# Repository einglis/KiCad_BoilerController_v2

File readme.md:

# Boiler Controller mk2

A whole new controller retaining the original features:

* Delayed closing valves
* Support for 24vac Nest thermostat (early US model)

And several new features:

* Multiple heating channels (zoned heating)
* ESP8266 for control and scheduling
* Greater flexibility in stat to valve mappings

The main MCU is an ESP8266 running https://github.com/einglis/SimpleNode/tree/main/examples/heating (still a WIP at the time of writing)

The valve controller is an Arduino Nano running https://github.com/einglis/boiler_valves

## HW versions

The first main board (control) had lots of drill holes that were too small; its replacement addesssed this and tidied up a few little details.

The first MCU board had pads that were too tiny to practically solder the transistors; its replacement added bigger pads, deleted the on-board status LEDs (since the MCUs have thier own), and simplified the ctrl+stat selector for the Hot Water valve.

Both replacements fixed an embarassing error where I hadn't read the ordering instructions, leaving a "Order Number Here" label present on both boards  ...along with the actual order numbers.

## v2.1 Pictures

## v2.0 Pictures

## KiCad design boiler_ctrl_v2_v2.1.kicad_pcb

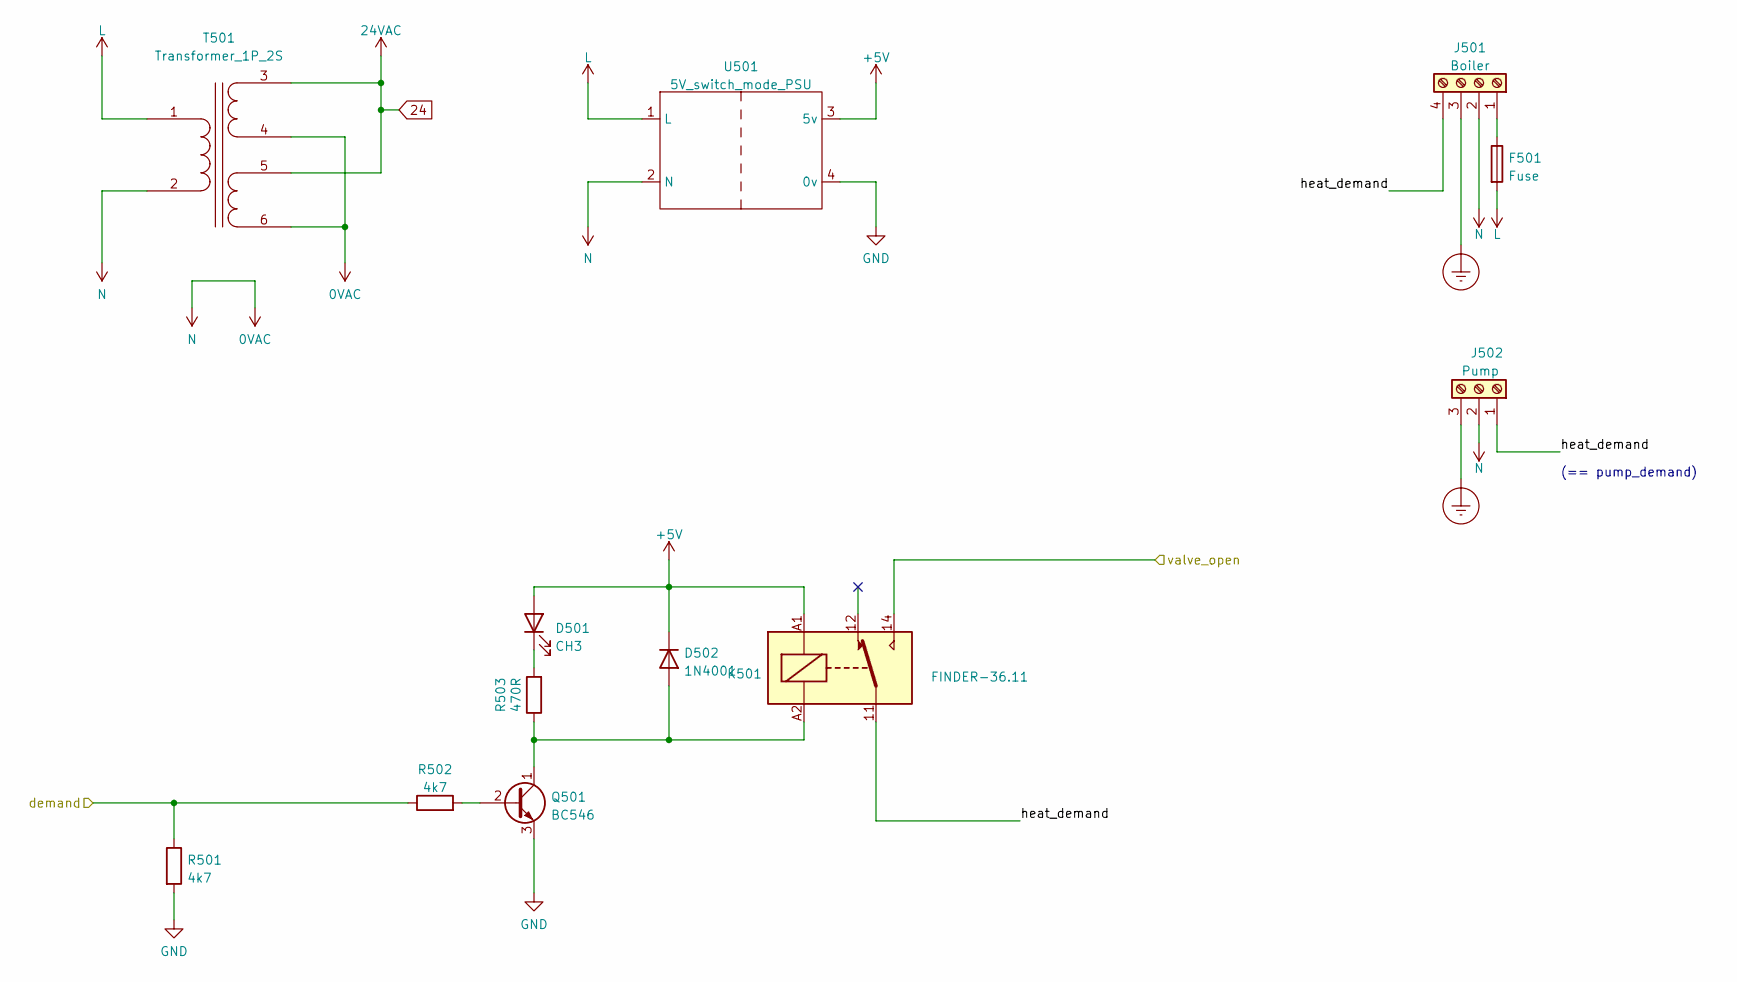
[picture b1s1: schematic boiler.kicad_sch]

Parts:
D501: CH3; LED_1206_3216Metric_Pad1.42x1.75mm_HandSolder
D502: 1N4001; D_DO-41_SOD81_P12mm_Horizontal
F501: Fuse; MULTICORP MC000827
J501: Boiler; CAMDENBOSS CTB0700_4
J502: Pump; CAMDENBOSS CTB0700_3
K501: FINDER-36.11; Relay_SPDT_Finder_36.11
Q501: BC546; TO-92_Inline
R501, R502: 4k7; R_0805_2012Metric_Pad1.20x1.40mm_HandSolder
R503: 470R; R_0805_2012Metric_Pad1.20x1.40mm_HandSolder
T501: Transformer_1P_2S; BLOCK VB_2.8_2_15
U501: 5V_switch_mode_PSU; MYRRA 47122

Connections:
0VAC: J501.2, J502.2, T501.2 (AB), T501.4 (SB), T501.6 (SD), U501.2 (N); also elsewhere on the board
24: T501.3 (SA), T501.5 (SC); also elsewhere on the board
/Boiler etc/heat_demand: J501.4, J502.1, K501.11
/Boiler etc/valve_open: K501.14; also elsewhere on the board
/boiler_demand: R501.1, R502.1; also elsewhere on the board
Earth_Protective: J501.3, J502.3; also elsewhere on the board
GND: Q501.3 (E), R501.2, U501.4 (0v); also elsewhere on the board
LINE: F501.2, T501.1 (AA), U501.1 (L); also elsewhere on the board
unnamed: D501.1 (K), R503.2
unnamed: D502.2 (A), K501.A2, Q501.1 (C), R503.1
unnamed: F501.1, J501.1
unnamed: Q501.2 (B), R502.2

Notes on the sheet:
(== pump_demand)

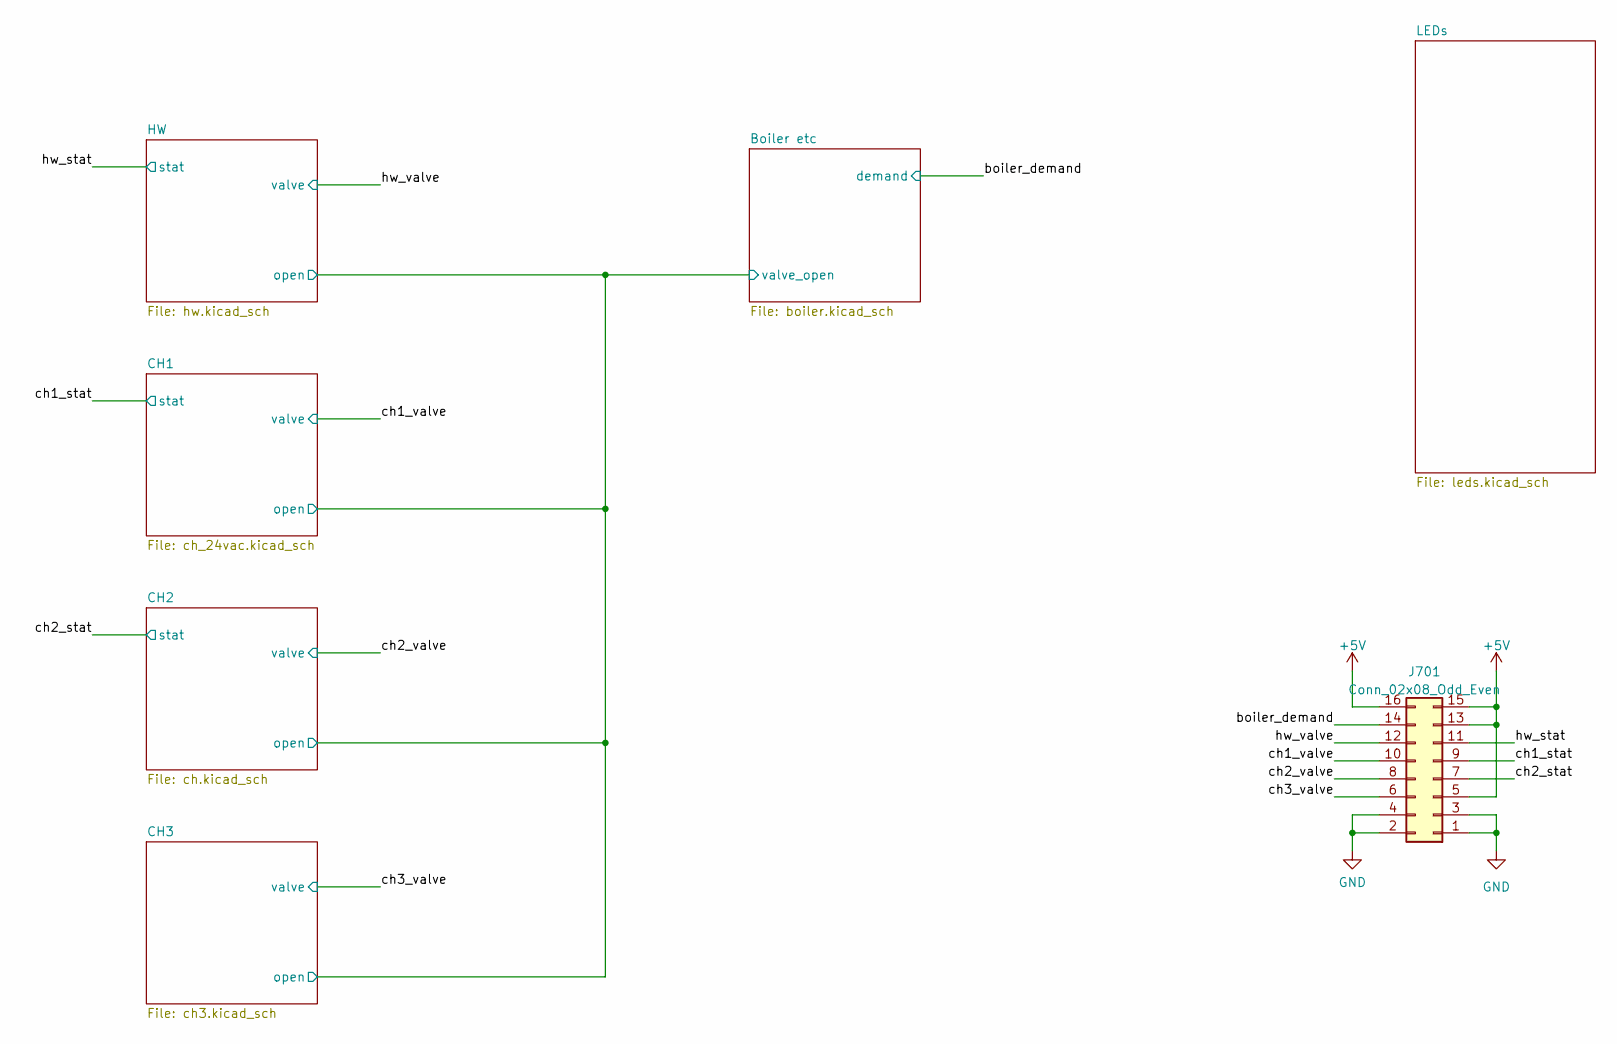
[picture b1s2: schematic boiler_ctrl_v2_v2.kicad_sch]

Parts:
J701: Conn_02x08_Odd_Even; PinHeader_2x08_P2.54mm_Vertical

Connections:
/boiler_demand: J701.14; also elsewhere on the board
/ch1_stat: J701.9; also elsewhere on the board
/ch1_valve: J701.10; also elsewhere on the board
/ch2_stat: J701.7; also elsewhere on the board
/ch2_valve: J701.8; also elsewhere on the board
/ch3_valve: J701.6; also elsewhere on the board
/hw_stat: J701.11; also elsewhere on the board
/hw_valve: J701.12; also elsewhere on the board
GND: J701.1, J701.2, J701.3, J701.4; also elsewhere on the board

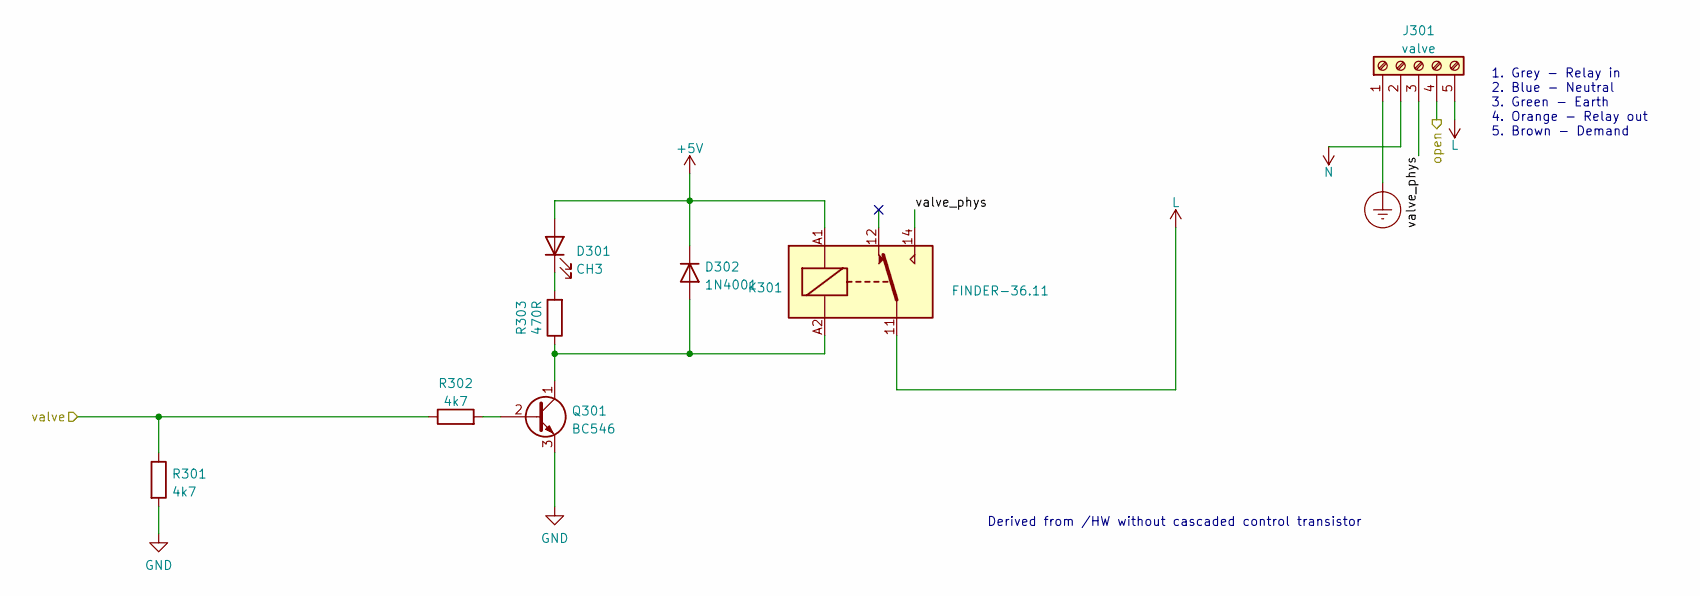
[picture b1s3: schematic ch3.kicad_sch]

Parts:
D301: CH3; LED_1206_3216Metric_Pad1.42x1.75mm_HandSolder
D302: 1N4001; D_DO-41_SOD81_P12mm_Horizontal
J301: valve; CAMDENBOSS CTB0700_5
K301: FINDER-36.11; Relay_SPDT_Finder_36.11
Q301: BC546; TO-92_Inline
R301, R302: 4k7; R_0805_2012Metric_Pad1.20x1.40mm_HandSolder
R303: 470R; R_0805_2012Metric_Pad1.20x1.40mm_HandSolder

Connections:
0VAC: J301.2; also elsewhere on the board
/Boiler etc/valve_open: J301.4; also elsewhere on the board
/CH3/valve_phys: J301.3, K301.14
/ch3_valve: R301.1, R302.1; also elsewhere on the board
Earth_Protective: J301.1; also elsewhere on the board
GND: Q301.3 (E), R301.2; also elsewhere on the board
LINE: J301.5, K301.11; also elsewhere on the board
unnamed: D301.1 (K), R303.2
unnamed: D302.2 (A), K301.A2, Q301.1 (C), R303.1
unnamed: Q301.2 (B), R302.2

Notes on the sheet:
Derived from /HW without cascaded control transistor
1. Grey - Relay in 2. Blue - Neutral 3. Green - Earth 4. Orange - Relay out 5. Brown - Demand

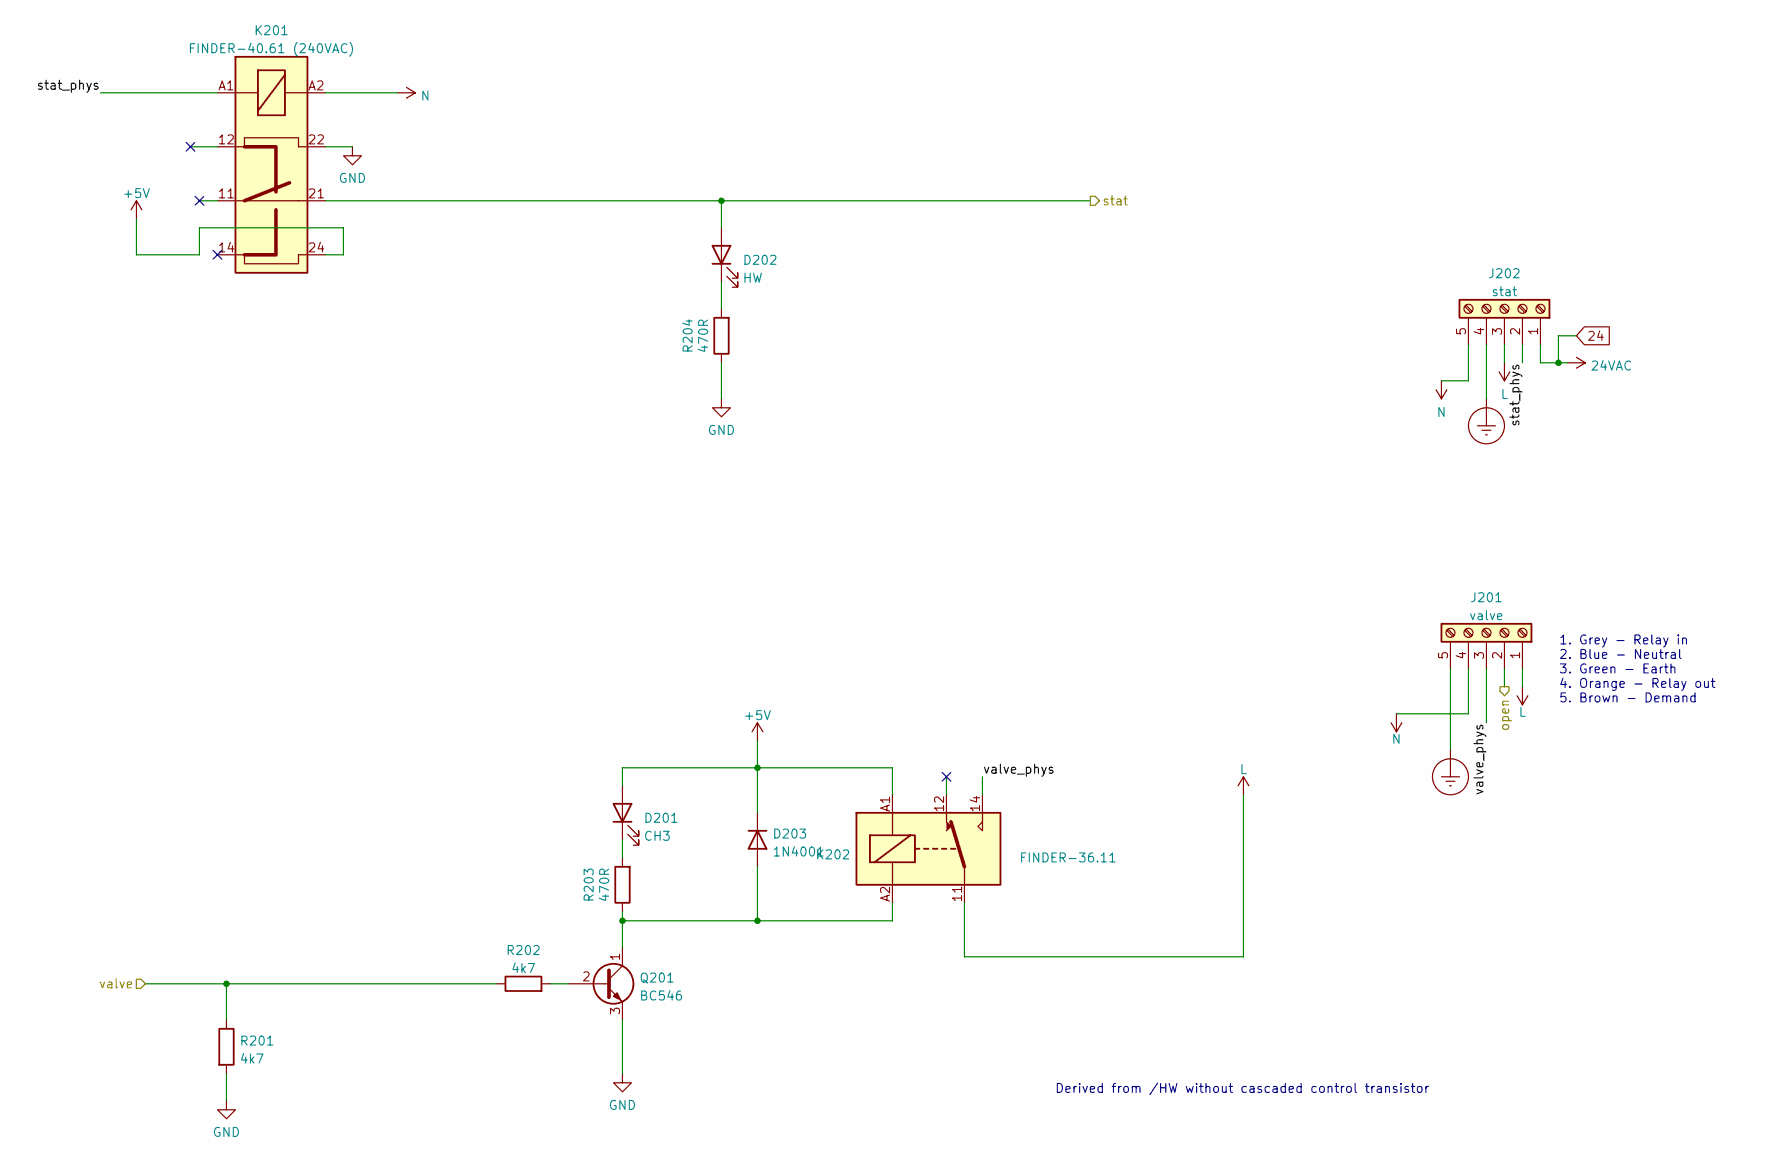
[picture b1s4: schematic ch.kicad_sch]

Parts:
D201: CH3; LED_1206_3216Metric_Pad1.42x1.75mm_HandSolder
D202: HW; LED_1206_3216Metric_Pad1.42x1.75mm_HandSolder
D203: 1N4001; D_DO-41_SOD81_P12mm_Horizontal
J201: valve; CAMDENBOSS CTB0700_5
J202: stat; CAMDENBOSS CTB0700_5
K201: FINDER-40.61 (240VAC); FINDER 40.61
K202: FINDER-36.11; Relay_SPDT_Finder_36.11
Q201: BC546; TO-92_Inline
R201, R202: 4k7; R_0805_2012Metric_Pad1.20x1.40mm_HandSolder
R203, R204: 470R; R_0805_2012Metric_Pad1.20x1.40mm_HandSolder

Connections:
0VAC: J201.4, J202.5, K201.A2; also elsewhere on the board
24: J202.1; also elsewhere on the board
/Boiler etc/valve_open: J201.2; also elsewhere on the board
/CH2/stat_phys: J202.2, K201.A1
/CH2/valve_phys: J201.3, K202.14
/ch2_stat: D202.2 (A), K201.21; also elsewhere on the board
/ch2_valve: R201.1, R202.1; also elsewhere on the board
Earth_Protective: J201.5, J202.4; also elsewhere on the board
GND: K201.22, Q201.3 (E), R201.2, R204.1; also elsewhere on the board
LINE: J201.1, J202.3, K202.11; also elsewhere on the board
unnamed: D201.1 (K), R203.2
unnamed: D202.1 (K), R204.2
unnamed: D203.2 (A), K202.A2, Q201.1 (C), R203.1
unnamed: Q201.2 (B), R202.2

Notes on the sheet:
Derived from /HW without cascaded control transistor
1. Grey - Relay in 2. Blue - Neutral 3. Green - Earth 4. Orange - Relay out 5. Brown - Demand

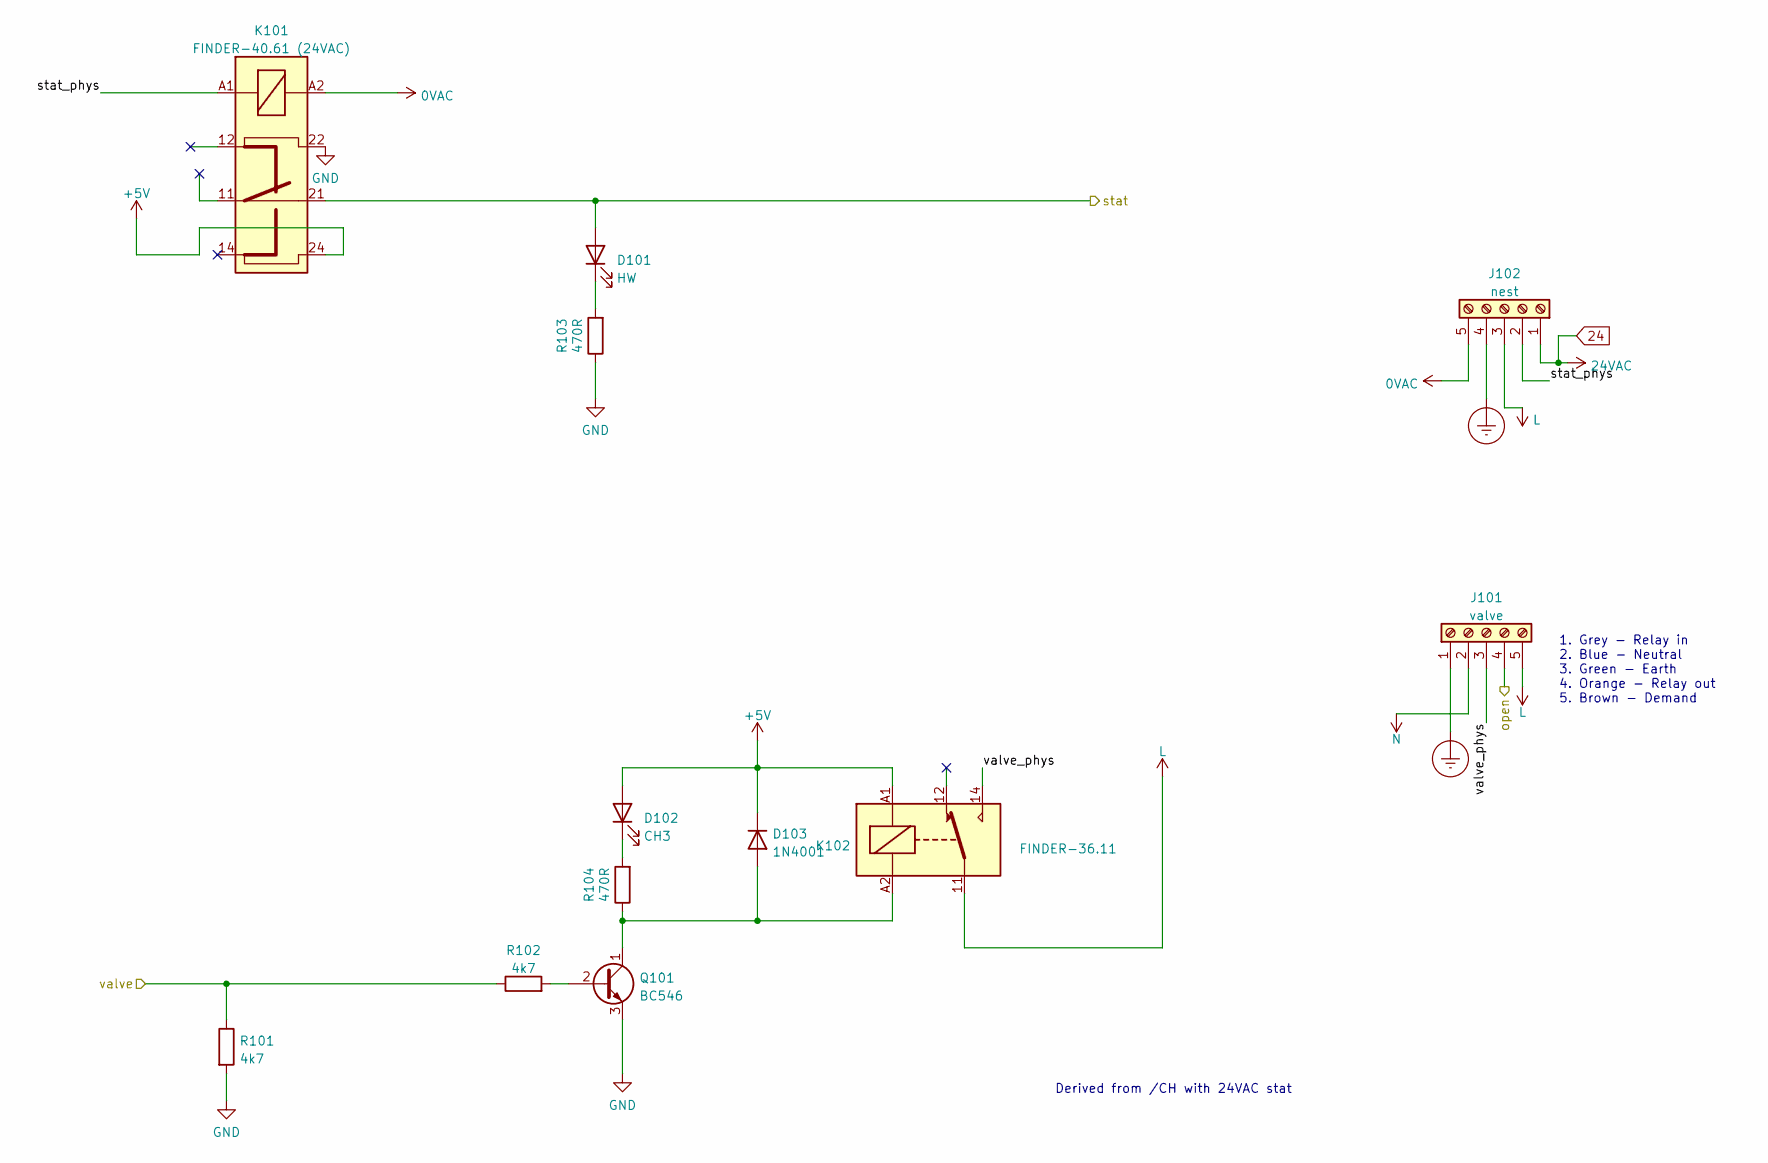
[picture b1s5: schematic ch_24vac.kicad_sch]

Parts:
D101: HW; LED_1206_3216Metric_Pad1.42x1.75mm_HandSolder
D102: CH3; LED_1206_3216Metric_Pad1.42x1.75mm_HandSolder
D103: 1N4001; D_DO-41_SOD81_P12mm_Horizontal
J101: valve; CAMDENBOSS CTB0700_5
J102: nest; CAMDENBOSS CTB0700_5
K101: FINDER-40.61 (24VAC); FINDER 40.61
K102: FINDER-36.11; Relay_SPDT_Finder_36.11
Q101: BC546; TO-92_Inline
R101, R102: 4k7; R_0805_2012Metric_Pad1.20x1.40mm_HandSolder
R103, R104: 470R; R_0805_2012Metric_Pad1.20x1.40mm_HandSolder

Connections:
0VAC: J101.2, J102.5, K101.A2; also elsewhere on the board
24: J102.1; also elsewhere on the board
/Boiler etc/valve_open: J101.4; also elsewhere on the board
/CH1/stat_phys: J102.2, K101.A1
/CH1/valve_phys: J101.3, K102.14
/ch1_stat: D101.2 (A), K101.21; also elsewhere on the board
/ch1_valve: R101.1, R102.1; also elsewhere on the board
Earth_Protective: J101.1, J102.4; also elsewhere on the board
GND: K101.22, Q101.3 (E), R101.2, R103.1; also elsewhere on the board
LINE: J101.5, J102.3, K102.11; also elsewhere on the board
unnamed: D101.1 (K), R103.2
unnamed: D102.1 (K), R104.2
unnamed: D103.2 (A), K102.A2, Q101.1 (C), R104.1
unnamed: Q101.2 (B), R102.2

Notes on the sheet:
Derived from /CH with 24VAC stat
1. Grey - Relay in 2. Blue - Neutral 3. Green - Earth 4. Orange - Relay out 5. Brown - Demand

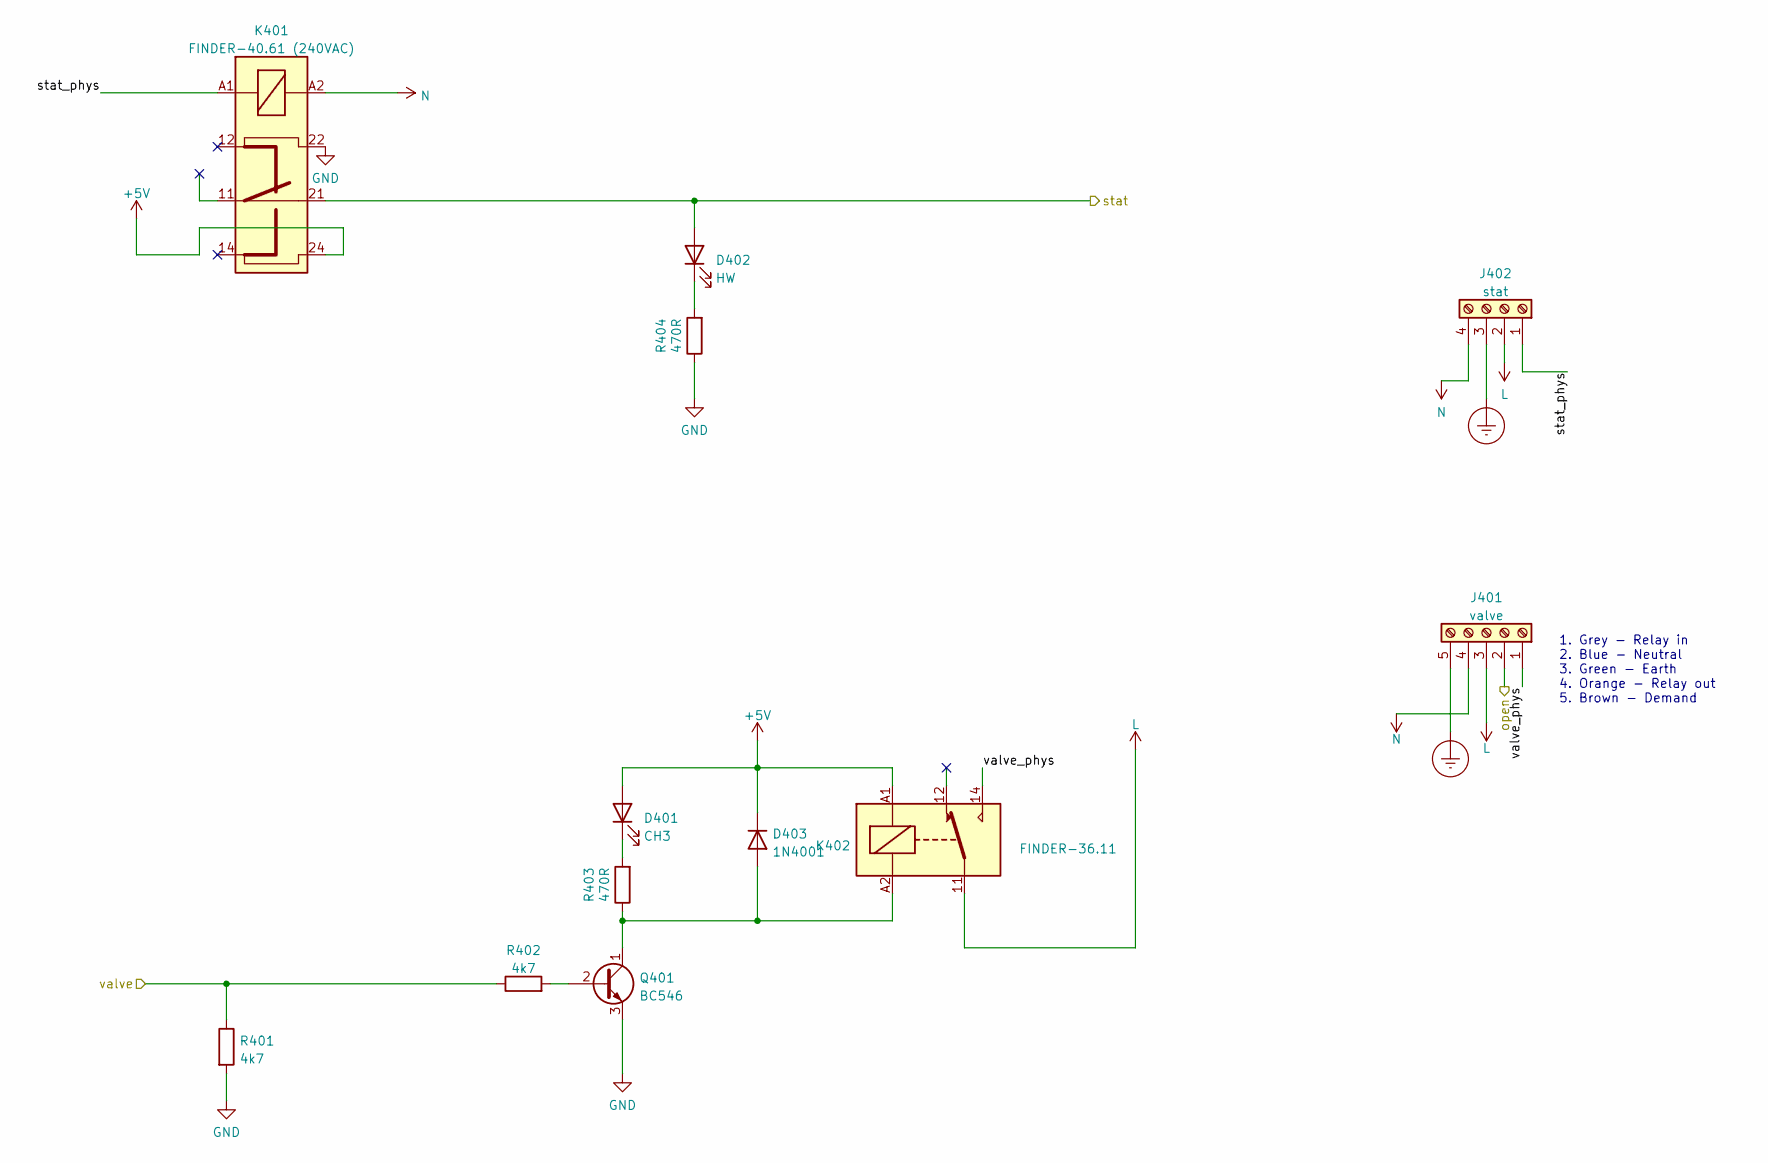
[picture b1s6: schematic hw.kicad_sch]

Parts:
D401: CH3; LED_1206_3216Metric_Pad1.42x1.75mm_HandSolder
D402: HW; LED_1206_3216Metric_Pad1.42x1.75mm_HandSolder
D403: 1N4001; D_DO-41_SOD81_P12mm_Horizontal
J401: valve; CAMDENBOSS CTB0700_5
J402: stat; CAMDENBOSS CTB0700_4
K401: FINDER-40.61 (240VAC); FINDER 40.61
K402: FINDER-36.11; Relay_SPDT_Finder_36.11
Q401: BC546; TO-92_Inline
R401, R402: 4k7; R_0805_2012Metric_Pad1.20x1.40mm_HandSolder
R403, R404: 470R; R_0805_2012Metric_Pad1.20x1.40mm_HandSolder

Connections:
0VAC: J401.4, J402.4, K401.A2; also elsewhere on the board
/Boiler etc/valve_open: J401.2; also elsewhere on the board
/HW/stat_phys: J402.1, K401.A1
/HW/valve_phys: J401.1, K402.14
/hw_stat: D402.2 (A), K401.21; also elsewhere on the board
/hw_valve: R401.1, R402.1; also elsewhere on the board
Earth_Protective: J401.5, J402.3; also elsewhere on the board
GND: K401.22, Q401.3 (E), R401.2, R404.1; also elsewhere on the board
LINE: J401.3, J402.2, K402.11; also elsewhere on the board
unnamed: D401.1 (K), R403.2
unnamed: D402.1 (K), R404.2
unnamed: D403.2 (A), K402.A2, Q401.1 (C), R403.1
unnamed: Q401.2 (B), R402.2

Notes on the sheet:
1. Grey - Relay in 2. Blue - Neutral 3. Green - Earth 4. Orange - Relay out 5. Brown - Demand

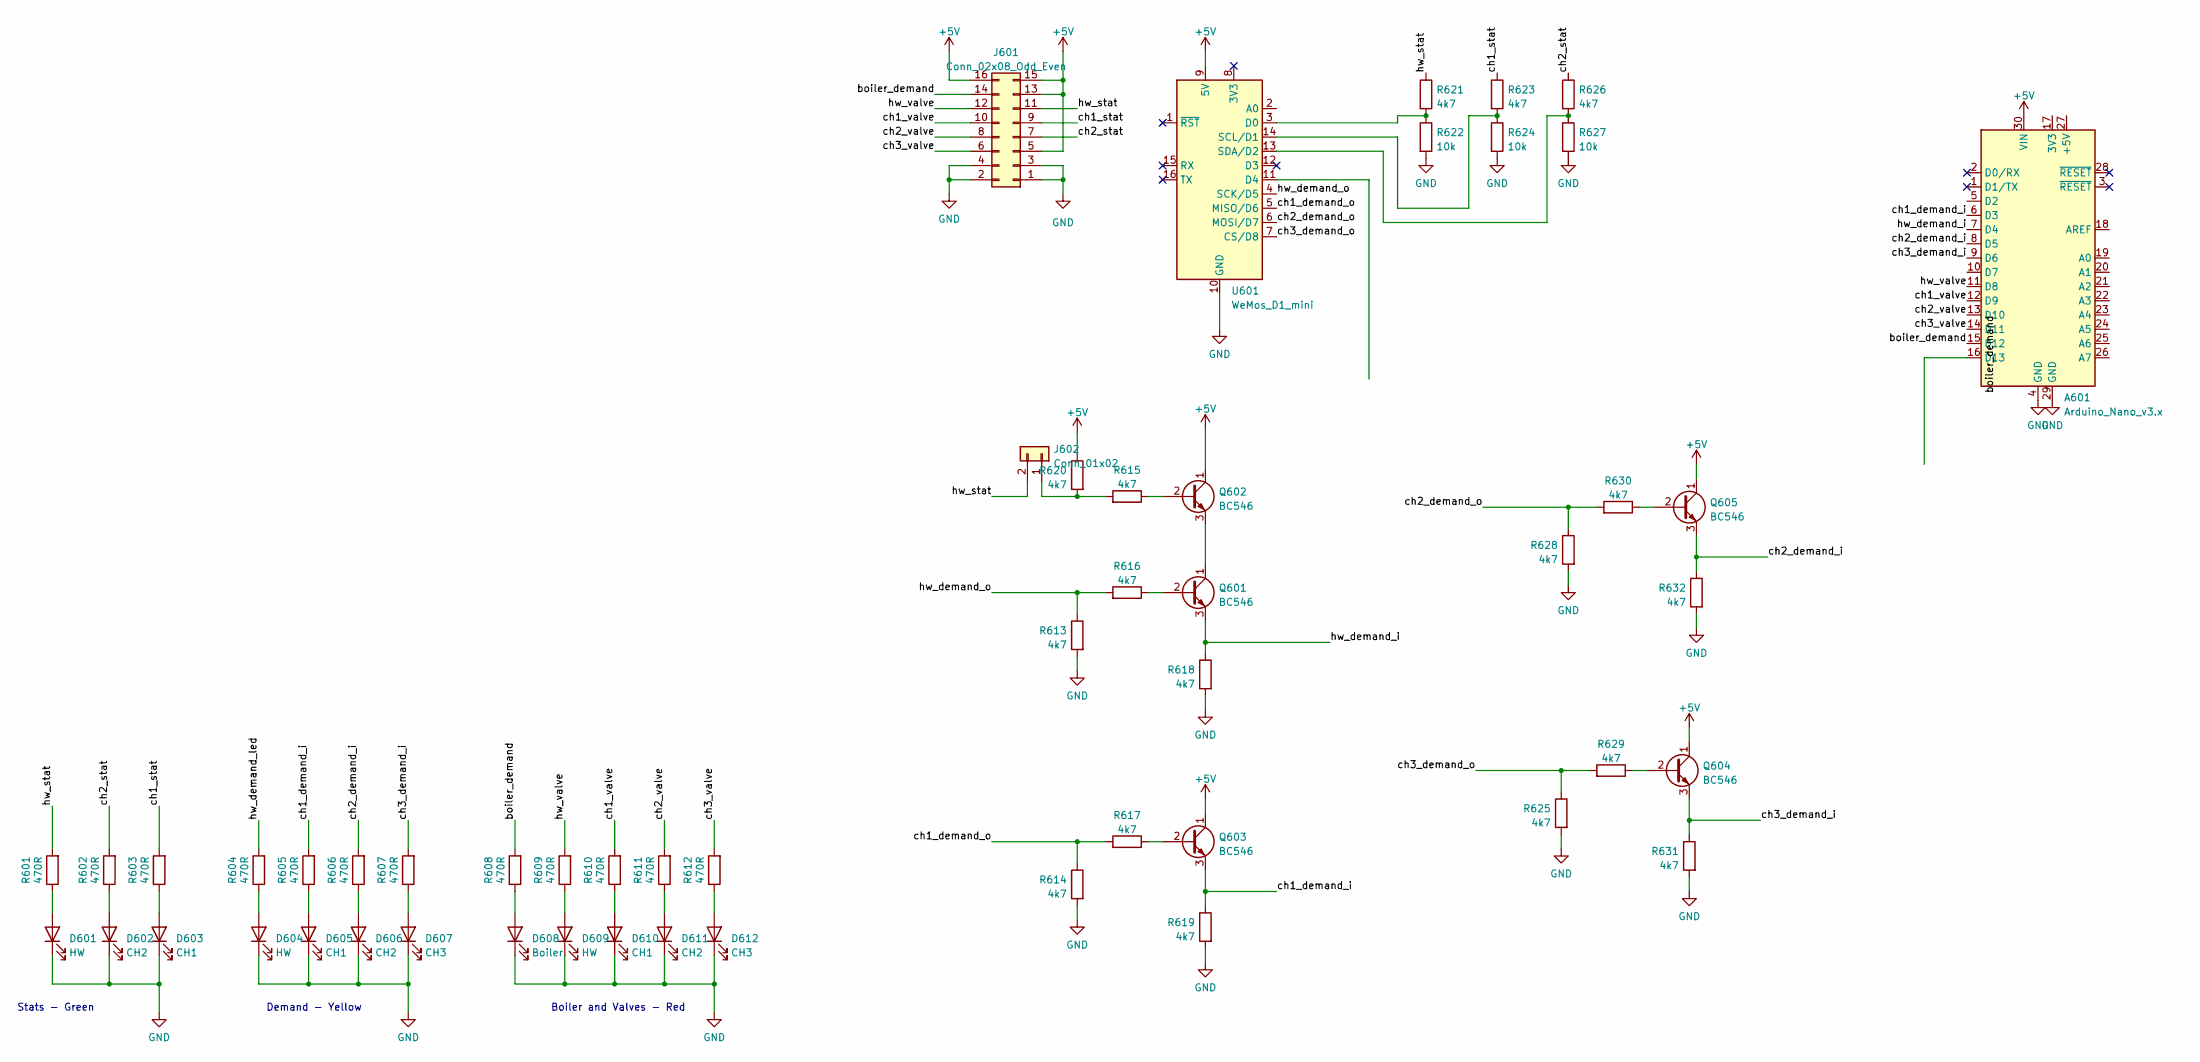
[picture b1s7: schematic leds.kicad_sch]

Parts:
A601: Arduino_Nano_v3.x; Arduino_Nano
D601, D604, D609: HW; LED_1206_3216Metric_Pad1.42x1.75mm_HandSolder
D602, D606, D611: CH2; LED_1206_3216Metric_Pad1.42x1.75mm_HandSolder
D603, D605, D610: CH1; LED_1206_3216Metric_Pad1.42x1.75mm_HandSolder
D607, D612: CH3; LED_1206_3216Metric_Pad1.42x1.75mm_HandSolder
D608: Boiler; LED_1206_3216Metric_Pad1.42x1.75mm_HandSolder
J601: Conn_02x08_Odd_Even; PinHeader_2x08_P2.54mm_Vertical
J602: Conn_01x02; PinHeader_1x02_P2.54mm_Vertical
Q601, Q602, Q603, Q604, Q605: BC546; TO-92_Inline
R601, R602, R603, R604, R605, R606, R607, R608, R609, R610, R611, R612: 470R; R_0805_2012Metric_Pad1.20x1.40mm_HandSolder
R613, R614, R615, R616, R617, R618, R619, R620, R621, R623, R625, R626, R628, R629, R630, R631, R632: 4k7; R_0805_2012Metric_Pad1.20x1.40mm_HandSolder
R622, R624, R627: 10k; R_0805_2012Metric_Pad1.20x1.40mm_HandSolder
U601: WeMos_D1_mini; WEMOS_D1_mini_light

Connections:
/LEDs/boiler_demand: A601.15 (D12), J601.14, R608.2
/LEDs/ch1_demand_i: A601.6 (D3), Q603.3 (E), R605.2, R619.1
/LEDs/ch1_demand_o: R614.1, R617.2, U601.5 (MISO/D6)
/LEDs/ch1_stat: J601.9, R603.2, R623.1
/LEDs/ch1_valve: A601.12 (D9), J601.10, R610.2
/LEDs/ch2_demand_i: A601.8 (D5), Q605.3 (E), R606.2, R632.1
/LEDs/ch2_demand_o: R628.1, R630.2, U601.6 (MOSI/D7)
/LEDs/ch2_stat: J601.7, R602.2, R626.1
/LEDs/ch2_valve: A601.13 (D10), J601.8, R611.2
/LEDs/ch3_demand_i: A601.9 (D6), Q604.3 (E), R607.2, R631.1
/LEDs/ch3_demand_o: R625.1, R629.2, U601.7 (CS/D8)
/LEDs/ch3_valve: A601.14 (D11), J601.6, R612.2
/LEDs/hw_demand_o: R613.1, R616.2, U601.4 (SCK/D5)
/LEDs/hw_stat: J601.11, J602.2, R601.2, R621.1
/LEDs/hw_valve: A601.11 (D8), J601.12, R609.2
GND: A601.4 (GND), A601.29 (GND), D601.1 (K), D602.1 (K), D603.1 (K), D604.1 (K), D605.1 (K), D606.1 (K), D607.1 (K), D608.1 (K), D609.1 (K), D610.1 (K), D611.1 (K), D612.1 (K), J601.1, J601.2, J601.3, J601.4, R613.2, R614.2, R618.2, R619.2, R622.2, R624.2, R625.2, R627.2, R628.2, R631.2, R632.2, U601.10 (GND); also elsewhere on the board
unnamed: D601.2 (A), R601.1
unnamed: D602.2 (A), R602.1
unnamed: D603.2 (A), R603.1
unnamed: D604.2 (A), R604.1
unnamed: D605.2 (A), R605.1
unnamed: D606.2 (A), R606.1
unnamed: D607.2 (A), R607.1
unnamed: D608.2 (A), R608.1
unnamed: D609.2 (A), R609.1
unnamed: D610.2 (A), R610.1
unnamed: D611.2 (A), R611.1
unnamed: D612.2 (A), R612.1
unnamed: Q603.2 (B), R617.1
unnamed: Q604.2 (B), R629.1
unnamed: Q605.2 (B), R630.1
unnamed: J602.1, R615.2, R620.2
unnamed: R621.2, R622.1, U601.3 (D0)
unnamed: R623.2, R624.1, U601.14 (SCL/D1)
unnamed: R626.2, R627.1, U601.13 (SDA/D2)

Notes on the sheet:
Boiler and Valves - Red
Demand - Yellow
Stats - Green

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
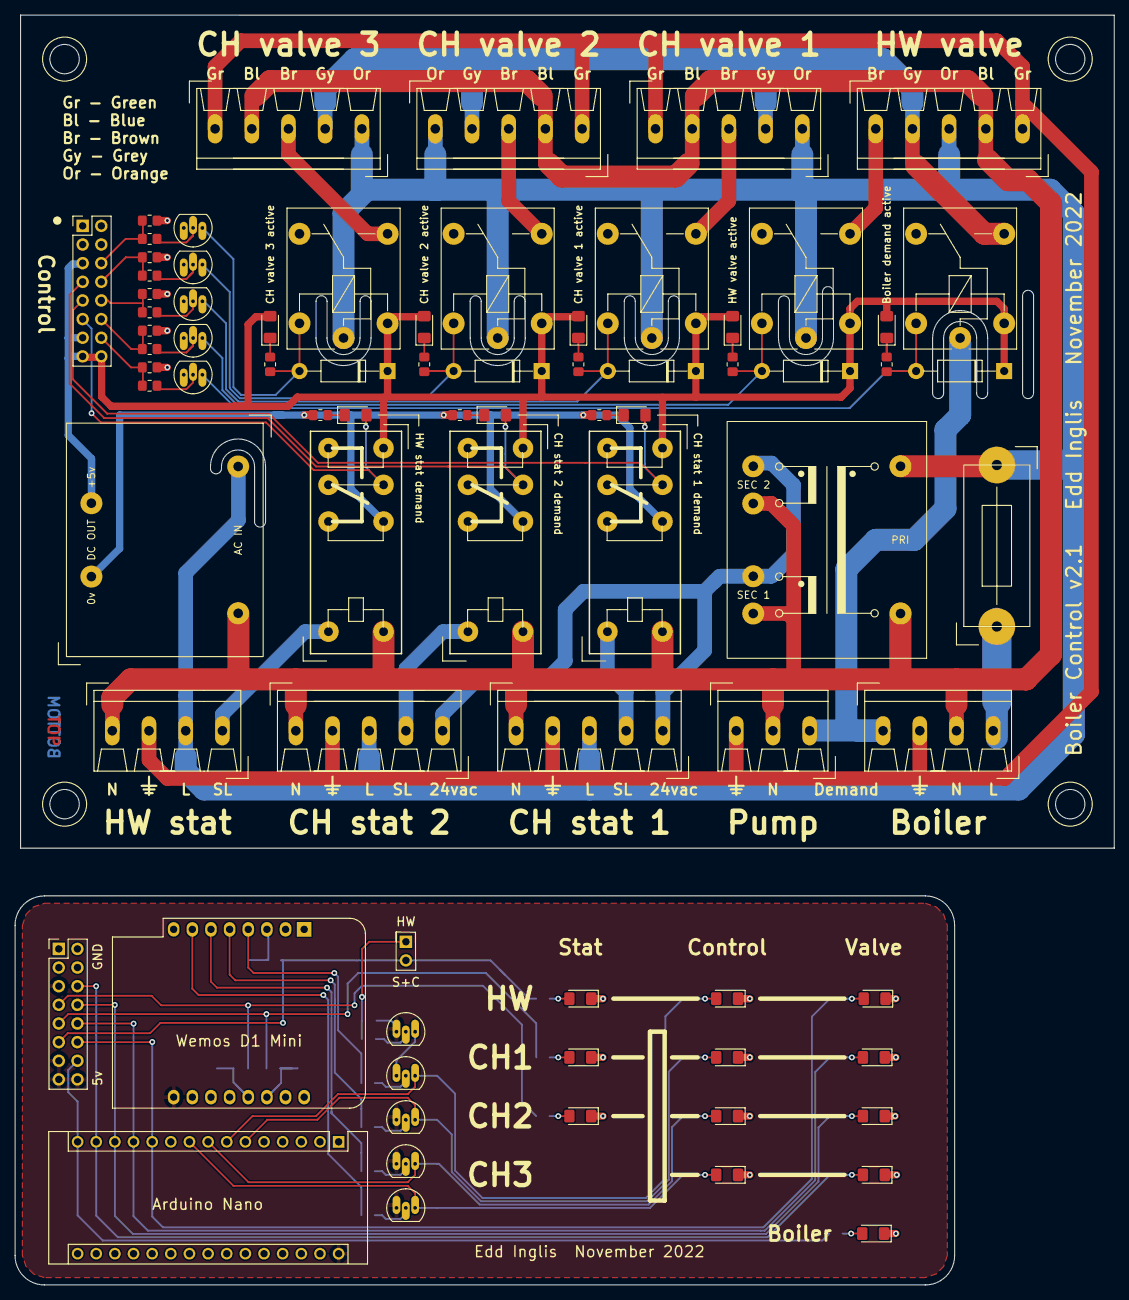
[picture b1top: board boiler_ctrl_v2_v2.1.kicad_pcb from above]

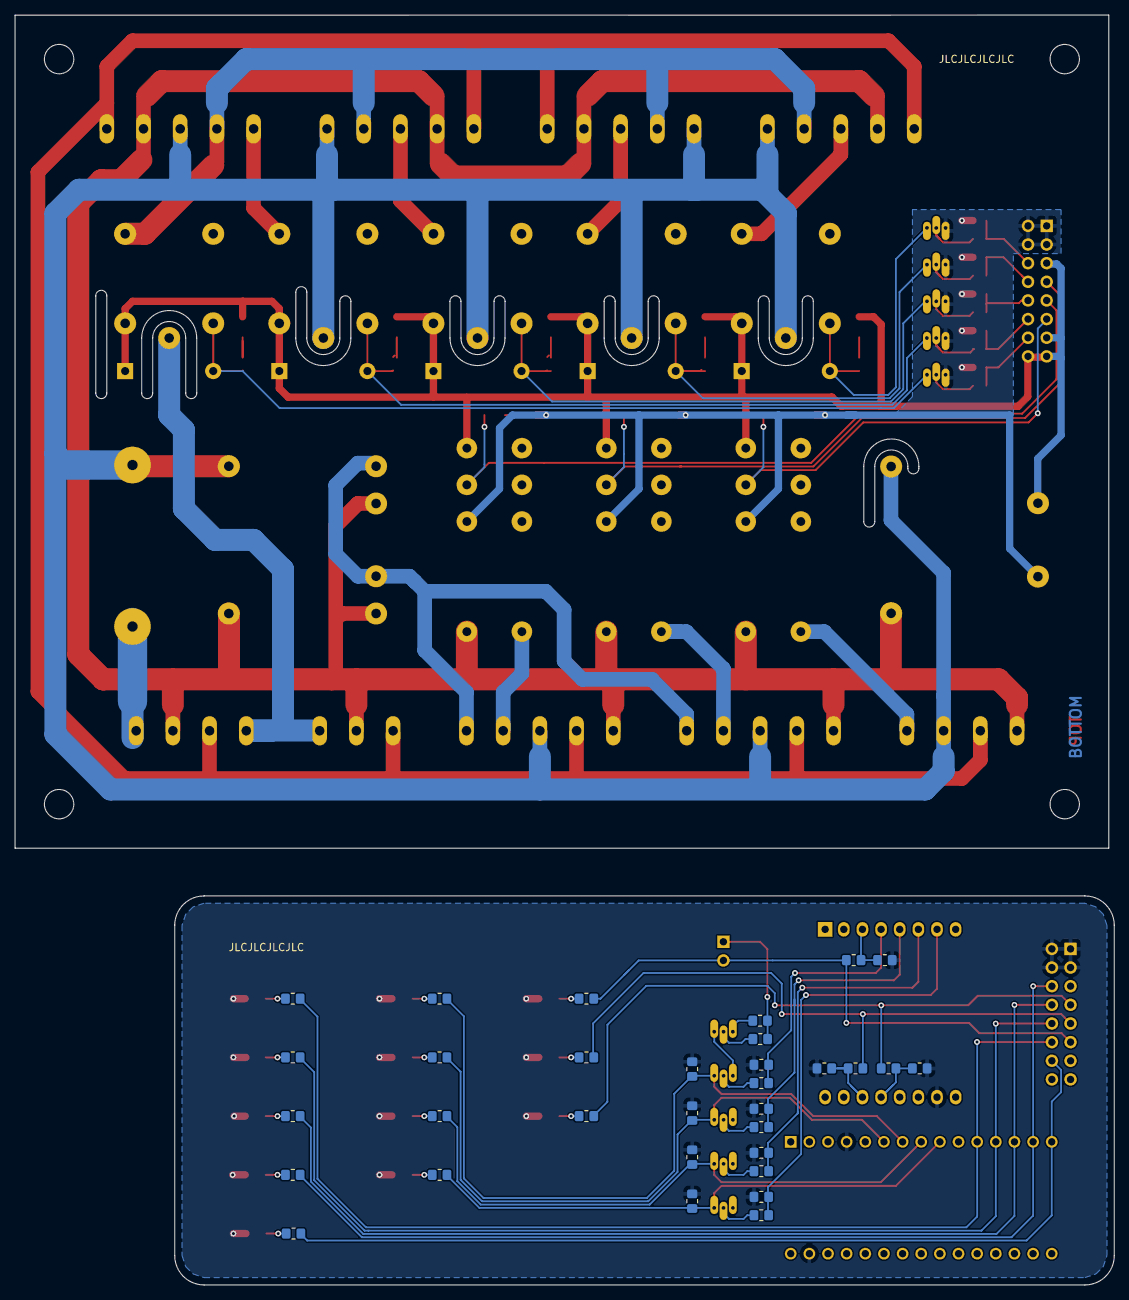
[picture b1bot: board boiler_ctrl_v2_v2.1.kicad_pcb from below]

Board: 4 copper layers, 149.8 x 173.0 mm, 110 parts (32 on the bottom side), 80 nets.

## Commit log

2023-12-16 pictures
